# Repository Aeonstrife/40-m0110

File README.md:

# 40-m0110 PCB
 
An OpenSource 40% PCB compatible with Ani's 40-m0110 case.  
Made for the Indian Mechanical Keyboard Community. 

## Layouts Supported  

## Firmware

### Building the firmware
Copy the folder "40m0110" from the firmware folder to your qmk_firmware/buildakb folder  
Launch QMK MSYS and run: `qmk compile -kb buildakb\40m0110 -km via`  
The firmware file will be created in qmk_firmware/.build folder  

### Flashing the firmware
Launch QMK Toolbox, Select MCU as ATmega32U2, select the firmware file and enable Auto-Flash checkbox.  
Press the reset button on the PCB to put the PCB in Bootloader mode.

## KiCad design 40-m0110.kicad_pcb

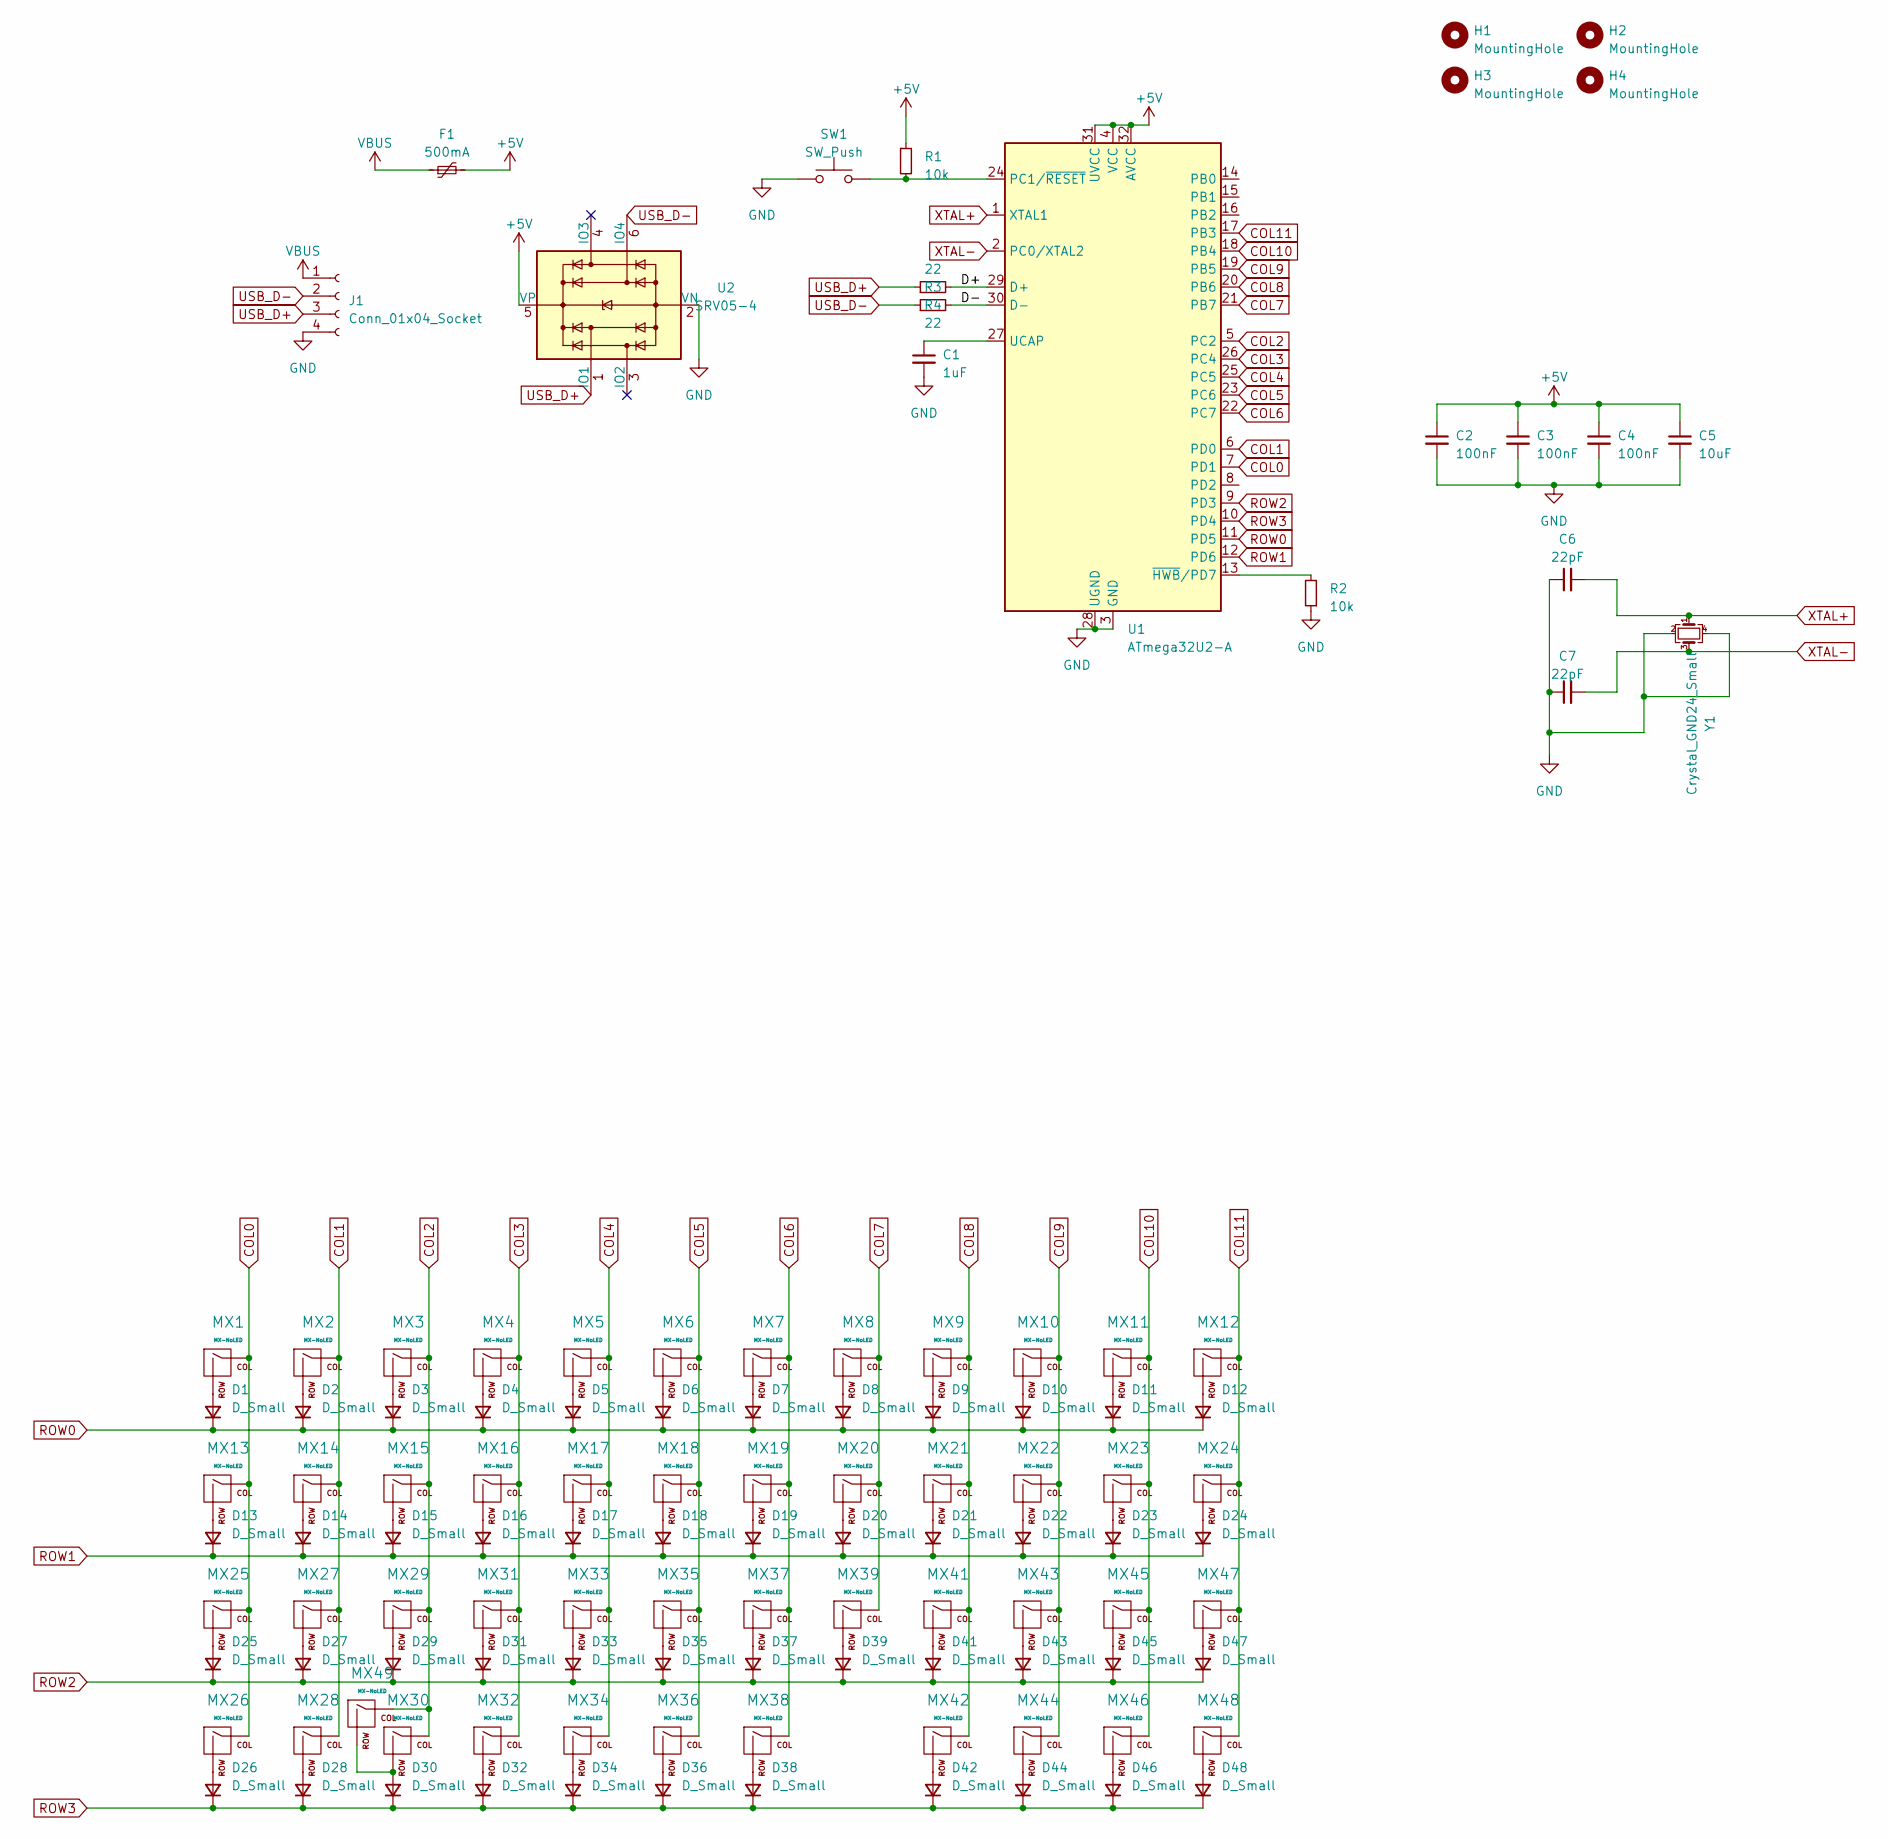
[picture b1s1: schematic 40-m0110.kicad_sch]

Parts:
C1: 1uF; C_0603_1608Metric
C2, C3, C4: 100nF; C_0603_1608Metric
C5: 10uF; C_0603_1608Metric
C6, C7: 22pF; C_0603_1608Metric
D1, D2, D3, D4, D5, D6, D7, D8, D9, D10, D11, D12, D13, D14, D15, D16, D17, D18, D19, D20, D21, D22, D23, D24, D25, D26, D27, D28, D29, D30, D31, D32, D33, D34, D35, D36, D37, D38, D39, D41, D42, D43, D44, D45, D46, D47, D48: D_Small; D_SOD-123
F1: 500mA; Fuse_0805_2012Metric
H1, H2, H3, H4: MountingHole; MountingHole_3.2mm_M3_DIN965_Pad
J1: Conn_01x04_Socket; SM04B-SRSS-TB(LF)(SN)_mounting-reliefs
MX1, MX2, MX3, MX4, MX5, MX6, MX7, MX8, MX9, MX10, MX11, MX12, MX13, MX14, MX15, MX16, MX17, MX18, MX19, MX20, MX21, MX22, MX23, MX24, MX25, MX26, MX27, MX28, MX29, MX30, MX31, MX32, MX33, MX34, MX35, MX36, MX37, MX38, MX39, MX41, MX42, MX43, MX44, MX45, MX46, MX47, MX48, MX49: MX-NoLED; MXOnly-1U-NoLED
R1, R2: 10k; R_0603_1608Metric
R3, R4: 22; R_0603_1608Metric
SW1: SW_Push; SW_SPST_TL3342
U1: ATmega32U2-A; TQFP-32_7x7mm_P0.8mm
U2: SRV05-4; SOT-23-6
Y1: Crystal_GND24_Small; Crystal_SMD_3225-4Pin_3.2x2.5mm

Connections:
+5V: C2.1, C3.1, C4.1, C5.1, F1.2, R1.1, U1.4 (VCC), U1.31 (UVCC), U1.32 (AVCC), U2.5 (VP)
/D+: R3.2, U1.29 (D+)
/D-: R4.2, U1.30 (D-)
COL0: MX1.1 (COL), MX13.1 (COL), MX25.1 (COL), MX26.1 (COL), U1.7 (PD1)
COL1: MX2.1 (COL), MX14.1 (COL), MX27.1 (COL), MX28.1 (COL), U1.6 (PD0)
COL2: MX3.1 (COL), MX15.1 (COL), MX29.1 (COL), MX30.1 (COL), MX49.1 (COL), U1.5 (PC2)
COL3: MX4.1 (COL), MX16.1 (COL), MX31.1 (COL), MX32.1 (COL), U1.26 (PC4)
COL4: MX5.1 (COL), MX17.1 (COL), MX33.1 (COL), MX34.1 (COL), U1.25 (PC5)
COL5: MX6.1 (COL), MX18.1 (COL), MX35.1 (COL), MX36.1 (COL), U1.23 (PC6)
COL6: MX7.1 (COL), MX19.1 (COL), MX37.1 (COL), MX38.1 (COL), U1.22 (PC7)
COL7: MX8.1 (COL), MX20.1 (COL), MX39.1 (COL), U1.21 (PB7)
COL8: MX9.1 (COL), MX21.1 (COL), MX41.1 (COL), MX42.1 (COL), U1.20 (PB6)
COL9: MX10.1 (COL), MX22.1 (COL), MX43.1 (COL), MX44.1 (COL), U1.19 (PB5)
COL10: MX11.1 (COL), MX23.1 (COL), MX45.1 (COL), MX46.1 (COL), U1.18 (PB4)
COL11: MX12.1 (COL), MX24.1 (COL), MX47.1 (COL), MX48.1 (COL), U1.17 (PB3)
GND: C1.2, C2.2, C3.2, C4.2, C5.2, C6.1, C7.1, J1.4, R2.1, SW1.1, U1.3 (GND), U1.28 (UGND), U2.2 (VN), Y1.2, Y1.4
unnamed: D1.2 (A), MX1.2 (ROW)
unnamed: D2.2 (A), MX2.2 (ROW)
unnamed: D3.2 (A), MX3.2 (ROW)
unnamed: D4.2 (A), MX4.2 (ROW)
unnamed: D5.2 (A), MX5.2 (ROW)
unnamed: D6.2 (A), MX6.2 (ROW)
unnamed: D7.2 (A), MX7.2 (ROW)
unnamed: D8.2 (A), MX8.2 (ROW)
unnamed: D9.2 (A), MX9.2 (ROW)
unnamed: D10.2 (A), MX10.2 (ROW)
unnamed: D11.2 (A), MX11.2 (ROW)
unnamed: D12.2 (A), MX12.2 (ROW)
unnamed: D13.2 (A), MX13.2 (ROW)
unnamed: D14.2 (A), MX14.2 (ROW)
unnamed: D15.2 (A), MX15.2 (ROW)
unnamed: D16.2 (A), MX16.2 (ROW)
unnamed: D17.2 (A), MX17.2 (ROW)
unnamed: D18.2 (A), MX18.2 (ROW)
unnamed: D19.2 (A), MX19.2 (ROW)
unnamed: D20.2 (A), MX20.2 (ROW)
unnamed: D21.2 (A), MX21.2 (ROW)
unnamed: D22.2 (A), MX22.2 (ROW)
unnamed: D23.2 (A), MX23.2 (ROW)
unnamed: D24.2 (A), MX24.2 (ROW)
unnamed: D25.2 (A), MX25.2 (ROW)
unnamed: D26.2 (A), MX26.2 (ROW)
unnamed: D27.2 (A), MX27.2 (ROW)
unnamed: D28.2 (A), MX28.2 (ROW)
unnamed: D29.2 (A), MX29.2 (ROW)
unnamed: D30.2 (A), MX30.2 (ROW), MX49.2 (ROW)
unnamed: D31.2 (A), MX31.2 (ROW)
unnamed: D32.2 (A), MX32.2 (ROW)
unnamed: D33.2 (A), MX33.2 (ROW)
unnamed: D34.2 (A), MX34.2 (ROW)
unnamed: D35.2 (A), MX35.2 (ROW)
unnamed: D36.2 (A), MX36.2 (ROW)
unnamed: D37.2 (A), MX37.2 (ROW)
unnamed: D38.2 (A), MX38.2 (ROW)
unnamed: D39.2 (A), MX39.2 (ROW)
unnamed: D41.2 (A), MX41.2 (ROW)
unnamed: D42.2 (A), MX42.2 (ROW)
unnamed: D43.2 (A), MX43.2 (ROW)
unnamed: D44.2 (A), MX44.2 (ROW)
unnamed: D45.2 (A), MX45.2 (ROW)
unnamed: D46.2 (A), MX46.2 (ROW)
unnamed: D47.2 (A), MX47.2 (ROW)
unnamed: D48.2 (A), MX48.2 (ROW)
unnamed: R1.2, SW1.2, U1.24 (PC1/~RESET)
unnamed: C1.1, U1.27 (UCAP)
unnamed: R2.2, U1.13 (~HWB/PD7)
ROW0: D1.1 (K), D2.1 (K), D3.1 (K), D4.1 (K), D5.1 (K), D6.1 (K), D7.1 (K), D8.1 (K), D9.1 (K), D10.1 (K), D11.1 (K), D12.1 (K), U1.11 (PD5)
ROW1: D13.1 (K), D14.1 (K), D15.1 (K), D16.1 (K), D17.1 (K), D18.1 (K), D19.1 (K), D20.1 (K), D21.1 (K), D22.1 (K), D23.1 (K), D24.1 (K), U1.12 (PD6)
ROW2: D25.1 (K), D27.1 (K), D29.1 (K), D31.1 (K), D33.1 (K), D35.1 (K), D37.1 (K), D39.1 (K), D41.1 (K), D43.1 (K), D45.1 (K), D47.1 (K), U1.9 (PD3)
ROW3: D26.1 (K), D28.1 (K), D30.1 (K), D32.1 (K), D34.1 (K), D36.1 (K), D38.1 (K), D42.1 (K), D44.1 (K), D46.1 (K), D48.1 (K), U1.10 (PD4)
USB_D+: J1.3, R3.1, U2.1 (IO1)
USB_D-: J1.2, R4.1, U2.6 (IO4)
VBUS: F1.1, J1.1
XTAL+: C6.2, U1.1 (XTAL1), Y1.1
XTAL-: C7.2, U1.2 (PC0/XTAL2), Y1.3

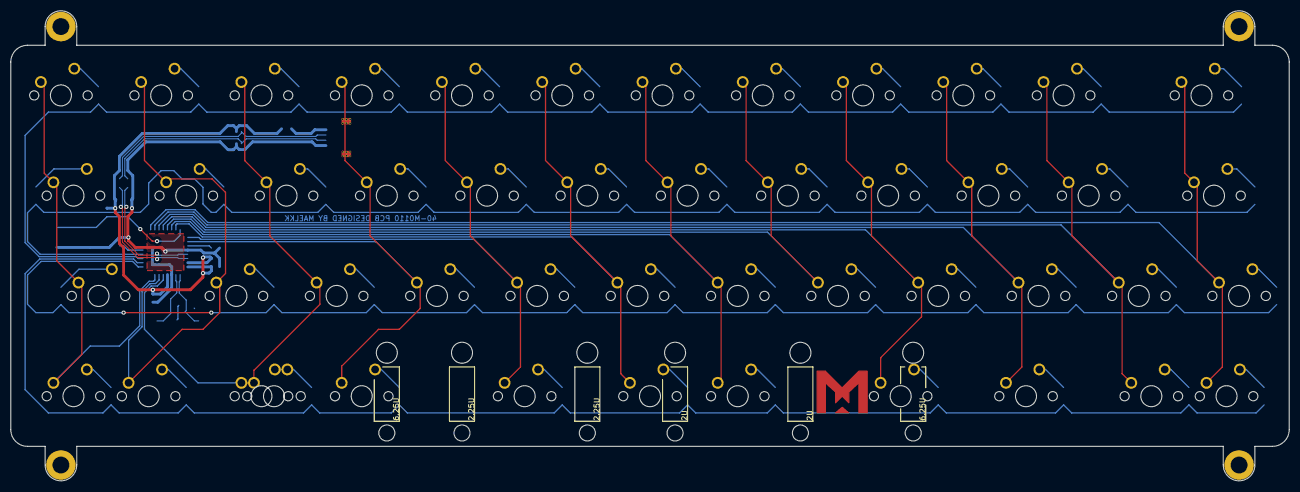
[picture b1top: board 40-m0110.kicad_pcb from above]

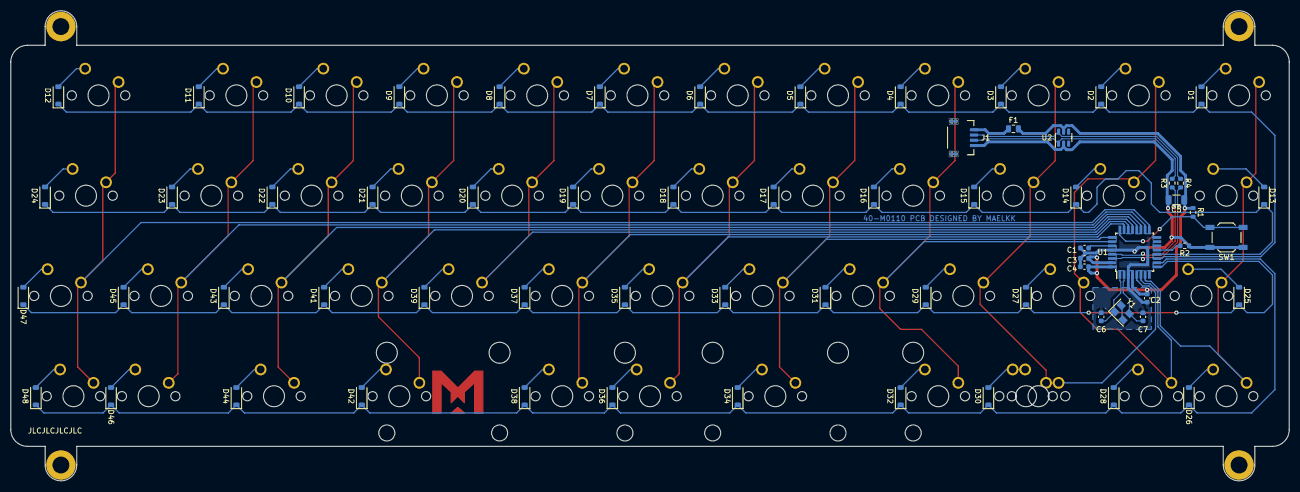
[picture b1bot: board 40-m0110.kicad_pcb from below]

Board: 2 copper layers, 242.9 x 89.3 mm, 116 parts (64 on the bottom side), 75 nets.

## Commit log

2023-03-10 Init files
2023-06-03 added firmware
